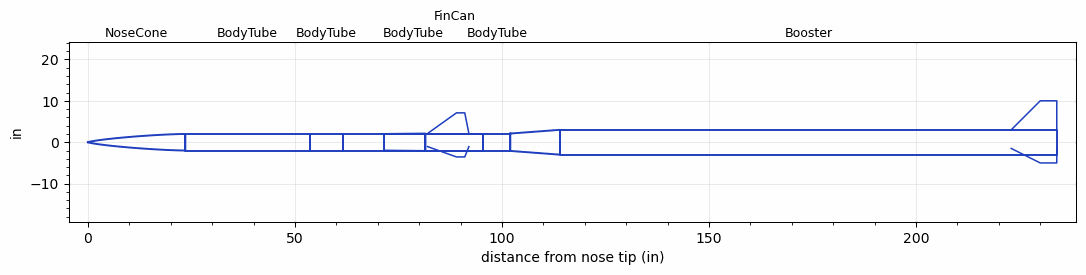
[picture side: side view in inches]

<RASAeroDocument>
 <FileVersion>2</FileVersion>
 <RocketDesign>
  <NoseCone>
   <Length>23.5</Length>
   <Diameter>4</Diameter>
   <Shape>Von Karman Ogive</Shape>
   <Location>0</Location>
  </NoseCone>
  <BodyTube>
   <Length>30</Length>
   <Diameter>4</Diameter>
   <Location>23.5</Location>
  </BodyTube>
  <BodyTube>
   <Length>8</Length>
   <Diameter>4</Diameter>
   <Location>53.5</Location>
  </BodyTube>
  <BodyTube>
   <Length>34</Length>
   <Diameter>4</Diameter>
   <Location>61.5</Location>
  </BodyTube>
  <FinCan>
   <Length>14</Length>
   <Diameter>4.2</Diameter>
   <InsideDiameter>4</InsideDiameter>
   <Location>95.5</Location>
   <ShoulderLength>10</ShoulderLength>
   <Offset>-14</Offset>
   <Fin>
    <Count>3</Count>
    <Chord>10</Chord>
    <Span>5</Span>
    <SweepDistance>7</SweepDistance>
    <TipChord>2</TipChord>
    <Thickness>0.34</Thickness>
    <LERadius>0.125</LERadius>
    <Location>13.5</Location>
    <AirfoilSection>Hexagonal</AirfoilSection>
    <FX1>0.5</FX1>
    <FX3>0.5</FX3>
   </Fin>
  </FinCan>
  <BodyTube>
   <Length>6.5</Length>
   <Diameter>4.2</Diameter>
   <Location>95.5</Location>
  </BodyTube>
  <Booster>
   <Length>120</Length>
   <Diameter>6</Diameter>
   <InsideDiameter>4.2</InsideDiameter>
   <Location>102</Location>
   <ShoulderLength>12</ShoulderLength>
   <Fin>
    <Count>3</Count>
    <Chord>11</Chord>
    <Span>7</Span>
    <SweepDistance>7</SweepDistance>
    <TipChord>4</TipChord>
    <Thickness>0.13</Thickness>
    <LERadius>0.125</LERadius>
    <Location>11</Location>
    <AirfoilSection>Hexagonal</AirfoilSection>
    <FX1>0.5</FX1>
    <FX3>0.5</FX3>
   </Fin>
  </Booster>
  <Surface>Smooth (Zero Roughness)</Surface>
  <ModifiedBarrowman>True</ModifiedBarrowman>
  <Turbulence>True</Turbulence>
  <UseBooster1>True</UseBooster1>
  <UseBooster2>False</UseBooster2>
 </RocketDesign>
 <LaunchSite>
  <Altitude>3000</Altitude>
  <Pressure>30.3</Pressure>
  <RodAngle>1</RodAngle>
  <RodLength>25</RodLength>
  <Temperature>90</Temperature>
  <WindSpeed>12</WindSpeed>
 </LaunchSite>
 <Recovery>
  <Altitude1>1000</Altitude1>
  <Altitude2>1000</Altitude2>
  <DeviceType1>None</DeviceType1>
  <DeviceType2>None</DeviceType2>
  <Event1>False</Event1>
  <Event2>False</Event2>
  <Size1>1</Size1>
  <Size2>1</Size2>
  <EventType1>None</EventType1>
  <EventType2>None</EventType2>
  <CD1>1.33</CD1>
  <CD2>1.33</CD2>
 </Recovery>
 <SimulationList>
  <Simulation>
   <SustainerEngine>BERMA-25000-02  (Karman_AIAA-capstone)</SustainerEngine>
   <SustainerLaunchWt>45</SustainerLaunchWt>
   <SustainerNozzleDiameter>3.9</SustainerNozzleDiameter>
   <SustainerCG>50.3</SustainerCG>
   <SustainerIgnitionDelay>9.5</SustainerIgnitionDelay>
   <Booster1Engine>O3400-IM-P  (CTI)</Booster1Engine>
   <Booster1LaunchWt>144</Booster1LaunchWt>
   <Booster1SeparationDelay>0.5</Booster1SeparationDelay>
   <Booster1IgnitionDelay>0</Booster1IgnitionDelay>
   <Booster1CG>135</Booster1CG>
   <Booster1NozzleDiameter>4.8</Booster1NozzleDiameter>
   <IncludeBooster1>True</IncludeBooster1>
   <Booster2Delay>0</Booster2Delay>
   <IncludeBooster2>False</IncludeBooster2>
   <TimetoApogee>110.7038</TimetoApogee>
   <MaxAltitude>169809.5</MaxAltitude>
   <MaxVelocity>5299.332</MaxVelocity>
  </Simulation>
  <Simulation>
   <SustainerEngine>BERMA-25000-02  (Karman_AIAA-capstone)</SustainerEngine>
   <SustainerLaunchWt>45</SustainerLaunchWt>
   <SustainerNozzleDiameter>3.9</SustainerNozzleDiameter>
   <SustainerCG>60</SustainerCG>
   <SustainerIgnitionDelay>23</SustainerIgnitionDelay>
   <Booster1LaunchWt>148</Booster1LaunchWt>
   <Booster1SeparationDelay>0.5</Booster1SeparationDelay>
   <Booster1IgnitionDelay>0</Booster1IgnitionDelay>
   <Booster1CG>105</Booster1CG>
   <Booster1NozzleDiameter>4.8</Booster1NozzleDiameter>
   <IncludeBooster1>False</IncludeBooster1>
   <Booster2Delay>0</Booster2Delay>
   <IncludeBooster2>False</IncludeBooster2>
   <TimetoApogee>60.93578</TimetoApogee>
   <MaxAltitude>80435.52</MaxAltitude>
   <MaxVelocity>4598.493</MaxVelocity>
  </Simulation>
  <Simulation>
   <SustainerEngine>BERMA-25000-02  (Karman_AIAA-capstone)</SustainerEngine>
   <SustainerLaunchWt>45</SustainerLaunchWt>
   <SustainerNozzleDiameter>3.9</SustainerNozzleDiameter>
   <SustainerCG>65</SustainerCG>
   <SustainerIgnitionDelay>10</SustainerIgnitionDelay>
   <Booster1Engine>O3400-IM-P  (CTI)</Booster1Engine>
   <Booster1LaunchWt>148</Booster1LaunchWt>
   <Booster1SeparationDelay>0.5</Booster1SeparationDelay>
   <Booster1IgnitionDelay>0</Booster1IgnitionDelay>
   <Booster1CG>105</Booster1CG>
   <Booster1NozzleDiameter>4.8</Booster1NozzleDiameter>
   <IncludeBooster1>True</IncludeBooster1>
   <Booster2Delay>0</Booster2Delay>
   <IncludeBooster2>False</IncludeBooster2>
   <TimetoApogee>131.3082</TimetoApogee>
   <MaxAltitude>230191.2</MaxAltitude>
   <MaxVelocity>5625.424</MaxVelocity>
  </Simulation>
 </SimulationList>
</RASAeroDocument>
